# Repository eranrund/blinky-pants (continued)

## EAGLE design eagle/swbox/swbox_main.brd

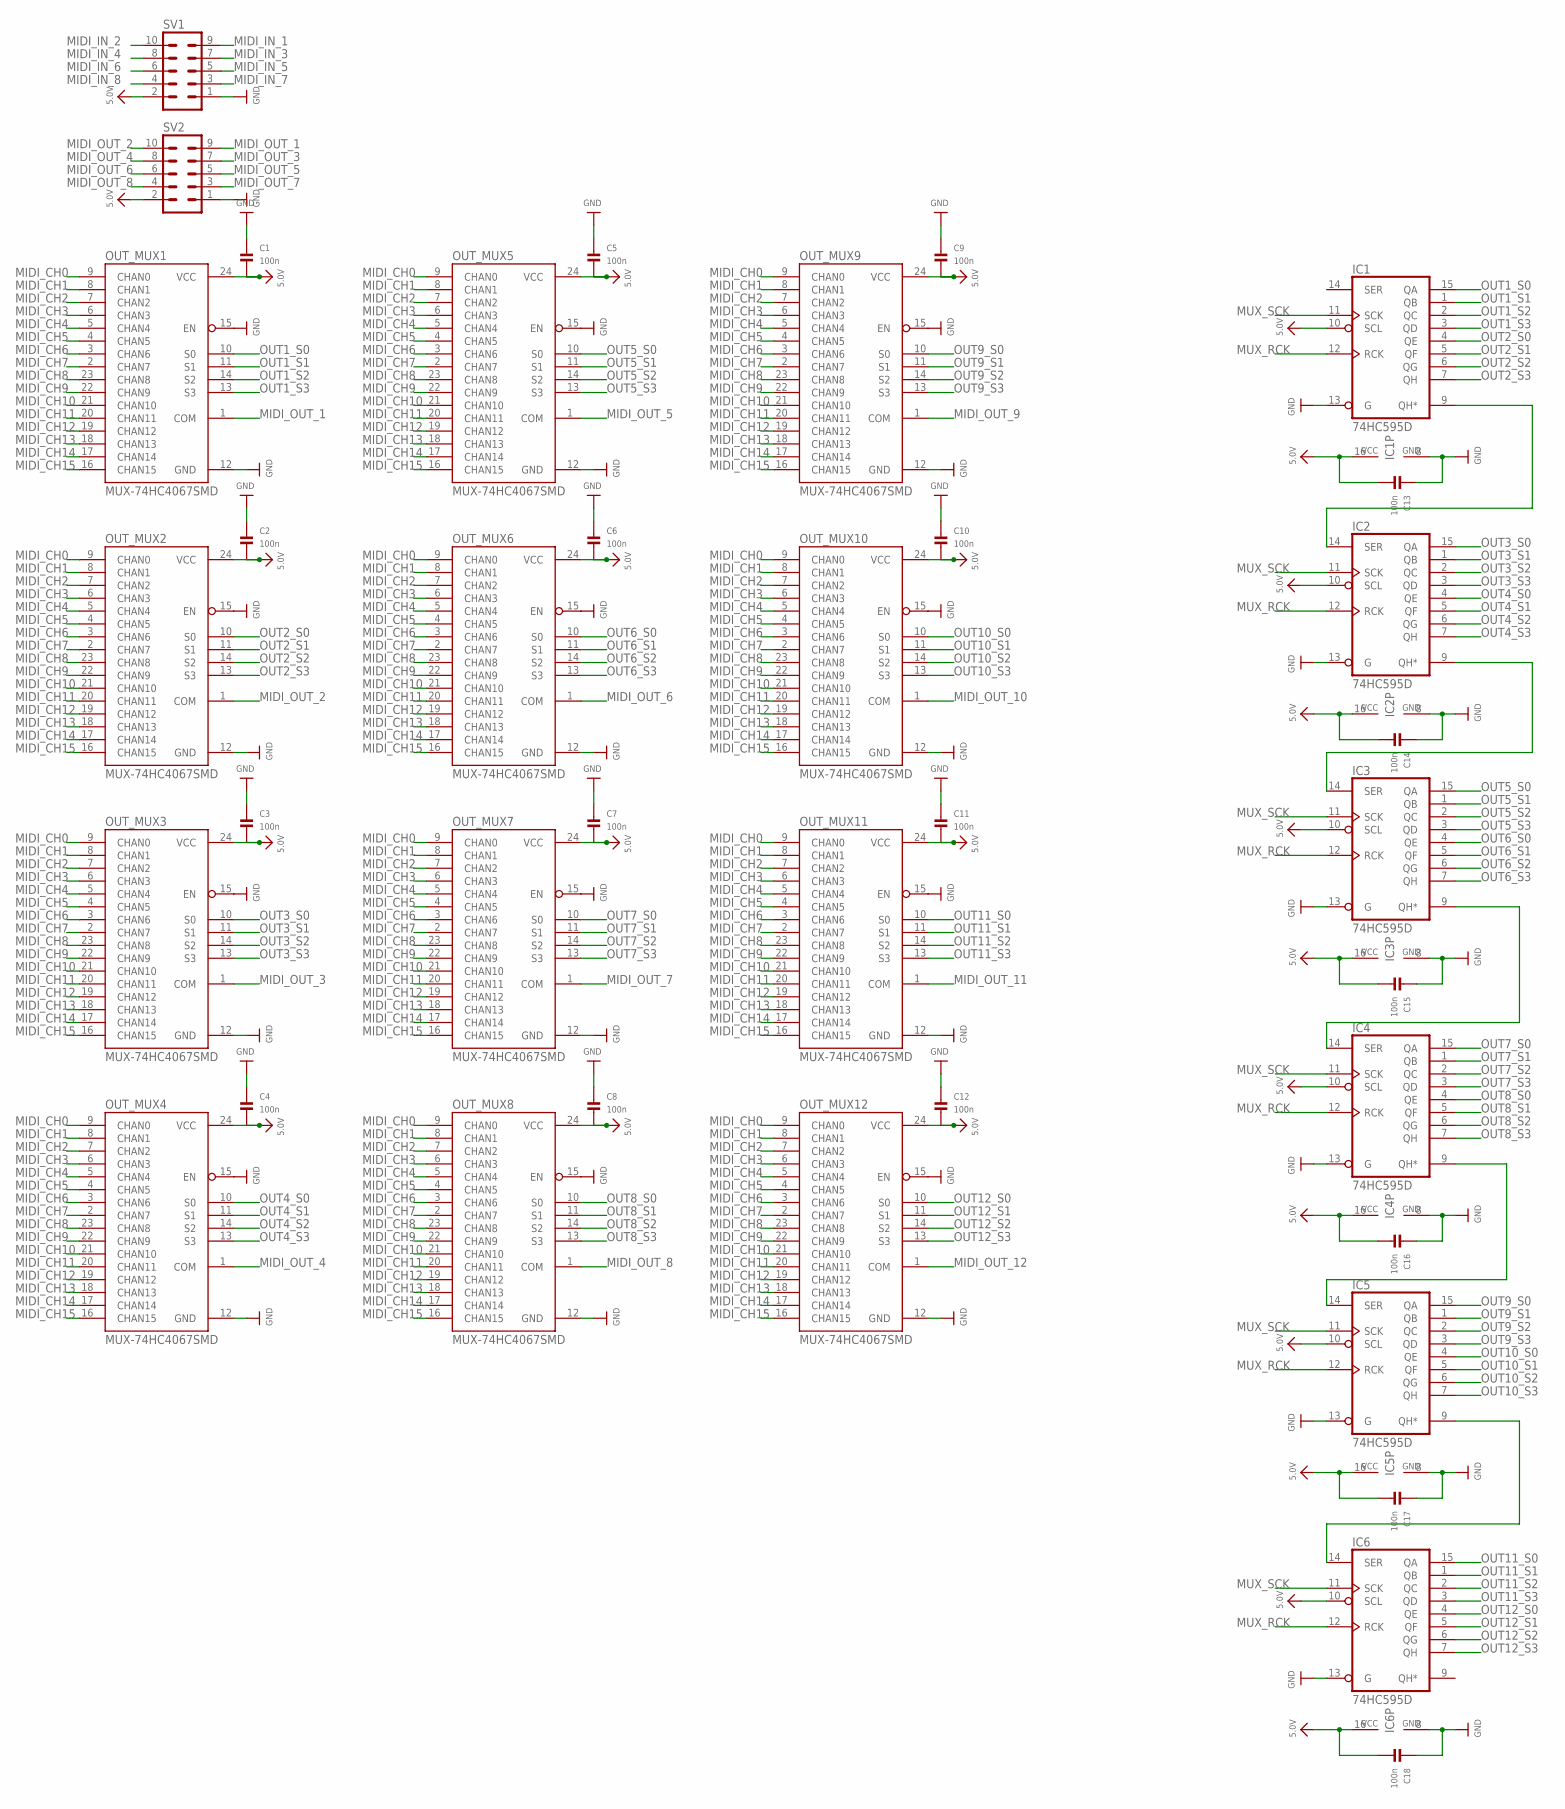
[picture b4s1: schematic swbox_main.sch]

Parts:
C1, C2, C3, C4, C5, C6, C7, C8, C9, C10, C11, C12, C13, C14, C15, C16, C17, C18: 100n; 0603
IC1, IC2, IC3, IC4, IC5, IC6: 74HC595D; SO16
OUT_MUX1, OUT_MUX2, OUT_MUX3, OUT_MUX4, OUT_MUX5, OUT_MUX6, OUT_MUX7, OUT_MUX8, OUT_MUX9, OUT_MUX10, OUT_MUX11, OUT_MUX12: MUX-74HC4067SMD; SSOP24
SV1, SV2: ML10

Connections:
5.0V: C1.2, C2.2, C3.2, C4.2, C5.2, C6.2, C7.2, C8.2, C9.2, C10.2, C11.2, C12.2, C13.2, C14.2, C15.2, C16.2, C17.2, C18.2, IC1.10 (SCL), IC1.16 (VCC), IC2.10 (SCL), IC2.16 (VCC), IC3.10 (SCL), IC3.16 (VCC), IC4.10 (SCL), IC4.16 (VCC), IC5.10 (SCL), IC5.16 (VCC), IC6.10 (SCL), IC6.16 (VCC), OUT_MUX1.24 (VCC), OUT_MUX2.24 (VCC), OUT_MUX3.24 (VCC), OUT_MUX4.24 (VCC), OUT_MUX5.24 (VCC), OUT_MUX6.24 (VCC), OUT_MUX7.24 (VCC), OUT_MUX8.24 (VCC), OUT_MUX9.24 (VCC), OUT_MUX10.24 (VCC), OUT_MUX11.24 (VCC), OUT_MUX12.24 (VCC), SV1.2, SV2.2
GND: C1.1, C2.1, C3.1, C4.1, C5.1, C6.1, C7.1, C8.1, C9.1, C10.1, C11.1, C12.1, C13.1, C14.1, C15.1, C16.1, C17.1, C18.1, IC1.8 (GND), IC1.13 (G), IC2.8 (GND), IC2.13 (G), IC3.8 (GND), IC3.13 (G), IC4.8 (GND), IC4.13 (G), IC5.8 (GND), IC5.13 (G), IC6.8 (GND), IC6.13 (G), OUT_MUX1.12 (GND), OUT_MUX1.15 (EN), OUT_MUX2.12 (GND), OUT_MUX2.15 (EN), OUT_MUX3.12 (GND), OUT_MUX3.15 (EN), OUT_MUX4.12 (GND), OUT_MUX4.15 (EN), OUT_MUX5.12 (GND), OUT_MUX5.15 (EN), OUT_MUX6.12 (GND), OUT_MUX6.15 (EN), OUT_MUX7.12 (GND), OUT_MUX7.15 (EN), OUT_MUX8.12 (GND), OUT_MUX8.15 (EN), OUT_MUX9.12 (GND), OUT_MUX9.15 (EN), OUT_MUX10.12 (GND), OUT_MUX10.15 (EN), OUT_MUX11.12 (GND), OUT_MUX11.15 (EN), OUT_MUX12.12 (GND), OUT_MUX12.15 (EN), SV1.1, SV2.1
MIDI_CH0: OUT_MUX1.9 (CHAN0), OUT_MUX2.9 (CHAN0), OUT_MUX3.9 (CHAN0), OUT_MUX4.9 (CHAN0), OUT_MUX5.9 (CHAN0), OUT_MUX6.9 (CHAN0), OUT_MUX7.9 (CHAN0), OUT_MUX8.9 (CHAN0), OUT_MUX9.9 (CHAN0), OUT_MUX10.9 (CHAN0), OUT_MUX11.9 (CHAN0), OUT_MUX12.9 (CHAN0)
MIDI_CH1: OUT_MUX1.8 (CHAN1), OUT_MUX2.8 (CHAN1), OUT_MUX3.8 (CHAN1), OUT_MUX4.8 (CHAN1), OUT_MUX5.8 (CHAN1), OUT_MUX6.8 (CHAN1), OUT_MUX7.8 (CHAN1), OUT_MUX8.8 (CHAN1), OUT_MUX9.8 (CHAN1), OUT_MUX10.8 (CHAN1), OUT_MUX11.8 (CHAN1), OUT_MUX12.8 (CHAN1)
MIDI_CH2: OUT_MUX1.7 (CHAN2), OUT_MUX2.7 (CHAN2), OUT_MUX3.7 (CHAN2), OUT_MUX4.7 (CHAN2), OUT_MUX5.7 (CHAN2), OUT_MUX6.7 (CHAN2), OUT_MUX7.7 (CHAN2), OUT_MUX8.7 (CHAN2), OUT_MUX9.7 (CHAN2), OUT_MUX10.7 (CHAN2), OUT_MUX11.7 (CHAN2), OUT_MUX12.7 (CHAN2)
MIDI_CH3: OUT_MUX1.6 (CHAN3), OUT_MUX2.6 (CHAN3), OUT_MUX3.6 (CHAN3), OUT_MUX4.6 (CHAN3), OUT_MUX5.6 (CHAN3), OUT_MUX6.6 (CHAN3), OUT_MUX7.6 (CHAN3), OUT_MUX8.6 (CHAN3), OUT_MUX9.6 (CHAN3), OUT_MUX10.6 (CHAN3), OUT_MUX11.6 (CHAN3), OUT_MUX12.6 (CHAN3)
MIDI_CH4: OUT_MUX1.5 (CHAN4), OUT_MUX2.5 (CHAN4), OUT_MUX3.5 (CHAN4), OUT_MUX4.5 (CHAN4), OUT_MUX5.5 (CHAN4), OUT_MUX6.5 (CHAN4), OUT_MUX7.5 (CHAN4), OUT_MUX8.5 (CHAN4), OUT_MUX9.5 (CHAN4), OUT_MUX10.5 (CHAN4), OUT_MUX11.5 (CHAN4), OUT_MUX12.5 (CHAN4)
MIDI_CH5: OUT_MUX1.4 (CHAN5), OUT_MUX2.4 (CHAN5), OUT_MUX3.4 (CHAN5), OUT_MUX4.4 (CHAN5), OUT_MUX5.4 (CHAN5), OUT_MUX6.4 (CHAN5), OUT_MUX7.4 (CHAN5), OUT_MUX8.4 (CHAN5), OUT_MUX9.4 (CHAN5), OUT_MUX10.4 (CHAN5), OUT_MUX11.4 (CHAN5), OUT_MUX12.4 (CHAN5)
MIDI_CH6: OUT_MUX1.3 (CHAN6), OUT_MUX2.3 (CHAN6), OUT_MUX3.3 (CHAN6), OUT_MUX4.3 (CHAN6), OUT_MUX5.3 (CHAN6), OUT_MUX6.3 (CHAN6), OUT_MUX7.3 (CHAN6), OUT_MUX8.3 (CHAN6), OUT_MUX9.3 (CHAN6), OUT_MUX10.3 (CHAN6), OUT_MUX11.3 (CHAN6), OUT_MUX12.3 (CHAN6)
MIDI_CH7: OUT_MUX1.2 (CHAN7), OUT_MUX2.2 (CHAN7), OUT_MUX3.2 (CHAN7), OUT_MUX4.2 (CHAN7), OUT_MUX5.2 (CHAN7), OUT_MUX6.2 (CHAN7), OUT_MUX7.2 (CHAN7), OUT_MUX8.2 (CHAN7), OUT_MUX9.2 (CHAN7), OUT_MUX10.2 (CHAN7), OUT_MUX11.2 (CHAN7), OUT_MUX12.2 (CHAN7)
MIDI_CH8: OUT_MUX1.23 (CHAN8), OUT_MUX2.23 (CHAN8), OUT_MUX3.23 (CHAN8), OUT_MUX4.23 (CHAN8), OUT_MUX5.23 (CHAN8), OUT_MUX6.23 (CHAN8), OUT_MUX7.23 (CHAN8), OUT_MUX8.23 (CHAN8), OUT_MUX9.23 (CHAN8), OUT_MUX10.23 (CHAN8), OUT_MUX11.23 (CHAN8), OUT_MUX12.23 (CHAN8)
MIDI_CH9: OUT_MUX1.22 (CHAN9), OUT_MUX2.22 (CHAN9), OUT_MUX3.22 (CHAN9), OUT_MUX4.22 (CHAN9), OUT_MUX5.22 (CHAN9), OUT_MUX6.22 (CHAN9), OUT_MUX7.22 (CHAN9), OUT_MUX8.22 (CHAN9), OUT_MUX9.22 (CHAN9), OUT_MUX10.22 (CHAN9), OUT_MUX11.22 (CHAN9), OUT_MUX12.22 (CHAN9)
MIDI_CH10: OUT_MUX1.21 (CHAN10), OUT_MUX2.21 (CHAN10), OUT_MUX3.21 (CHAN10), OUT_MUX4.21 (CHAN10), OUT_MUX5.21 (CHAN10), OUT_MUX6.21 (CHAN10), OUT_MUX7.21 (CHAN10), OUT_MUX8.21 (CHAN10), OUT_MUX9.21 (CHAN10), OUT_MUX10.21 (CHAN10), OUT_MUX11.21 (CHAN10), OUT_MUX12.21 (CHAN10)
MIDI_CH11: OUT_MUX1.20 (CHAN11), OUT_MUX2.20 (CHAN11), OUT_MUX3.20 (CHAN11), OUT_MUX4.20 (CHAN11), OUT_MUX5.20 (CHAN11), OUT_MUX6.20 (CHAN11), OUT_MUX7.20 (CHAN11), OUT_MUX8.20 (CHAN11), OUT_MUX9.20 (CHAN11), OUT_MUX10.20 (CHAN11), OUT_MUX11.20 (CHAN11), OUT_MUX12.20 (CHAN11)
MIDI_CH12: OUT_MUX1.19 (CHAN12), OUT_MUX2.19 (CHAN12), OUT_MUX3.19 (CHAN12), OUT_MUX4.19 (CHAN12), OUT_MUX5.19 (CHAN12), OUT_MUX6.19 (CHAN12), OUT_MUX7.19 (CHAN12), OUT_MUX8.19 (CHAN12), OUT_MUX9.19 (CHAN12), OUT_MUX10.19 (CHAN12), OUT_MUX11.19 (CHAN12), OUT_MUX12.19 (CHAN12)
MIDI_CH13: OUT_MUX1.18 (CHAN13), OUT_MUX2.18 (CHAN13), OUT_MUX3.18 (CHAN13), OUT_MUX4.18 (CHAN13), OUT_MUX5.18 (CHAN13), OUT_MUX6.18 (CHAN13), OUT_MUX7.18 (CHAN13), OUT_MUX8.18 (CHAN13), OUT_MUX9.18 (CHAN13), OUT_MUX10.18 (CHAN13), OUT_MUX11.18 (CHAN13), OUT_MUX12.18 (CHAN13)
MIDI_CH14: OUT_MUX1.17 (CHAN14), OUT_MUX2.17 (CHAN14), OUT_MUX3.17 (CHAN14), OUT_MUX4.17 (CHAN14), OUT_MUX5.17 (CHAN14), OUT_MUX6.17 (CHAN14), OUT_MUX7.17 (CHAN14), OUT_MUX8.17 (CHAN14), OUT_MUX9.17 (CHAN14), OUT_MUX10.17 (CHAN14), OUT_MUX11.17 (CHAN14), OUT_MUX12.17 (CHAN14)
MIDI_CH15: OUT_MUX1.16 (CHAN15), OUT_MUX2.16 (CHAN15), OUT_MUX3.16 (CHAN15), OUT_MUX4.16 (CHAN15), OUT_MUX5.16 (CHAN15), OUT_MUX6.16 (CHAN15), OUT_MUX7.16 (CHAN15), OUT_MUX8.16 (CHAN15), OUT_MUX9.16 (CHAN15), OUT_MUX10.16 (CHAN15), OUT_MUX11.16 (CHAN15), OUT_MUX12.16 (CHAN15)
MIDI_IN_1: SV1.9
MIDI_IN_2: SV1.10
MIDI_IN_3: SV1.7
MIDI_IN_4: SV1.8
MIDI_IN_5: SV1.5
MIDI_IN_6: SV1.6
MIDI_IN_7: SV1.3
MIDI_IN_8: SV1.4
MIDI_OUT_1: OUT_MUX1.1 (COM), SV2.9
MIDI_OUT_2: OUT_MUX2.1 (COM), SV2.10
MIDI_OUT_3: OUT_MUX3.1 (COM), SV2.7
MIDI_OUT_4: OUT_MUX4.1 (COM), SV2.8
MIDI_OUT_5: OUT_MUX5.1 (COM), SV2.5
MIDI_OUT_6: OUT_MUX6.1 (COM), SV2.6
MIDI_OUT_7: OUT_MUX7.1 (COM), SV2.3
MIDI_OUT_8: OUT_MUX8.1 (COM), SV2.4
MIDI_OUT_9: OUT_MUX9.1 (COM)
MIDI_OUT_10: OUT_MUX10.1 (COM)
MIDI_OUT_11: OUT_MUX11.1 (COM)
MIDI_OUT_12: OUT_MUX12.1 (COM)
MUX_RCK: IC1.12 (RCK), IC2.12 (RCK), IC3.12 (RCK), IC4.12 (RCK), IC5.12 (RCK), IC6.12 (RCK)
MUX_SCK: IC1.11 (SCK), IC2.11 (SCK), IC3.11 (SCK), IC4.11 (SCK), IC5.11 (SCK), IC6.11 (SCK)
unnamed: IC1.9 (QH*), IC2.14 (SER)
unnamed: IC2.9 (QH*), IC3.14 (SER)
unnamed: IC3.9 (QH*), IC4.14 (SER)
unnamed: IC4.9 (QH*), IC5.14 (SER)
unnamed: IC5.9 (QH*), IC6.14 (SER)
OUT1_S0: IC1.15 (QA), OUT_MUX1.10 (S0)
OUT1_S1: IC1.1 (QB), OUT_MUX1.11 (S1)
OUT1_S2: IC1.2 (QC), OUT_MUX1.14 (S2)
OUT1_S3: IC1.3 (QD), OUT_MUX1.13 (S3)
OUT2_S0: IC1.4 (QE), OUT_MUX2.10 (S0)
OUT2_S1: IC1.5 (QF), OUT_MUX2.11 (S1)
OUT2_S2: IC1.6 (QG), OUT_MUX2.14 (S2)
OUT2_S3: IC1.7 (QH), OUT_MUX2.13 (S3)
OUT3_S0: IC2.15 (QA), OUT_MUX3.10 (S0)
OUT3_S1: IC2.1 (QB), OUT_MUX3.11 (S1)
OUT3_S2: IC2.2 (QC), OUT_MUX3.14 (S2)
OUT3_S3: IC2.3 (QD), OUT_MUX3.13 (S3)
OUT4_S0: IC2.4 (QE), OUT_MUX4.10 (S0)
OUT4_S1: IC2.5 (QF), OUT_MUX4.11 (S1)
OUT4_S2: IC2.6 (QG), OUT_MUX4.14 (S2)
OUT4_S3: IC2.7 (QH), OUT_MUX4.13 (S3)
OUT5_S0: IC3.15 (QA), OUT_MUX5.10 (S0)
OUT5_S1: IC3.1 (QB), OUT_MUX5.11 (S1)
OUT5_S2: IC3.2 (QC), OUT_MUX5.14 (S2)
OUT5_S3: IC3.3 (QD), OUT_MUX5.13 (S3)
OUT6_S0: IC3.4 (QE), OUT_MUX6.10 (S0)
OUT6_S1: IC3.5 (QF), OUT_MUX6.11 (S1)
OUT6_S2: IC3.6 (QG), OUT_MUX6.14 (S2)
OUT6_S3: IC3.7 (QH), OUT_MUX6.13 (S3)
OUT7_S0: IC4.15 (QA), OUT_MUX7.10 (S0)
OUT7_S1: IC4.1 (QB), OUT_MUX7.11 (S1)
OUT7_S2: IC4.2 (QC), OUT_MUX7.14 (S2)
OUT7_S3: IC4.3 (QD), OUT_MUX7.13 (S3)
OUT8_S0: IC4.4 (QE), OUT_MUX8.10 (S0)
OUT8_S1: IC4.5 (QF), OUT_MUX8.11 (S1)
OUT8_S2: IC4.6 (QG), OUT_MUX8.14 (S2)
OUT8_S3: IC4.7 (QH), OUT_MUX8.13 (S3)
OUT9_S0: IC5.15 (QA), OUT_MUX9.10 (S0)
OUT9_S1: IC5.1 (QB), OUT_MUX9.11 (S1)
OUT9_S2: IC5.2 (QC), OUT_MUX9.14 (S2)
OUT9_S3: IC5.3 (QD), OUT_MUX9.13 (S3)
OUT10_S0: IC5.4 (QE), OUT_MUX10.10 (S0)
OUT10_S1: IC5.5 (QF), OUT_MUX10.11 (S1)
OUT10_S2: IC5.6 (QG), OUT_MUX10.14 (S2)
OUT10_S3: IC5.7 (QH), OUT_MUX10.13 (S3)
OUT11_S0: IC6.15 (QA), OUT_MUX11.10 (S0)
OUT11_S1: IC6.1 (QB), OUT_MUX11.11 (S1)
OUT11_S2: IC6.2 (QC), OUT_MUX11.14 (S2)
OUT11_S3: IC6.3 (QD), OUT_MUX11.13 (S3)
OUT12_S0: IC6.4 (QE), OUT_MUX12.10 (S0)
OUT12_S1: IC6.5 (QF), OUT_MUX12.11 (S1)
OUT12_S2: IC6.6 (QG), OUT_MUX12.14 (S2)
OUT12_S3: IC6.7 (QH), OUT_MUX12.13 (S3)

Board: 2 copper layers, 38 parts (0 on the bottom side), 81 nets, no tracks yet.

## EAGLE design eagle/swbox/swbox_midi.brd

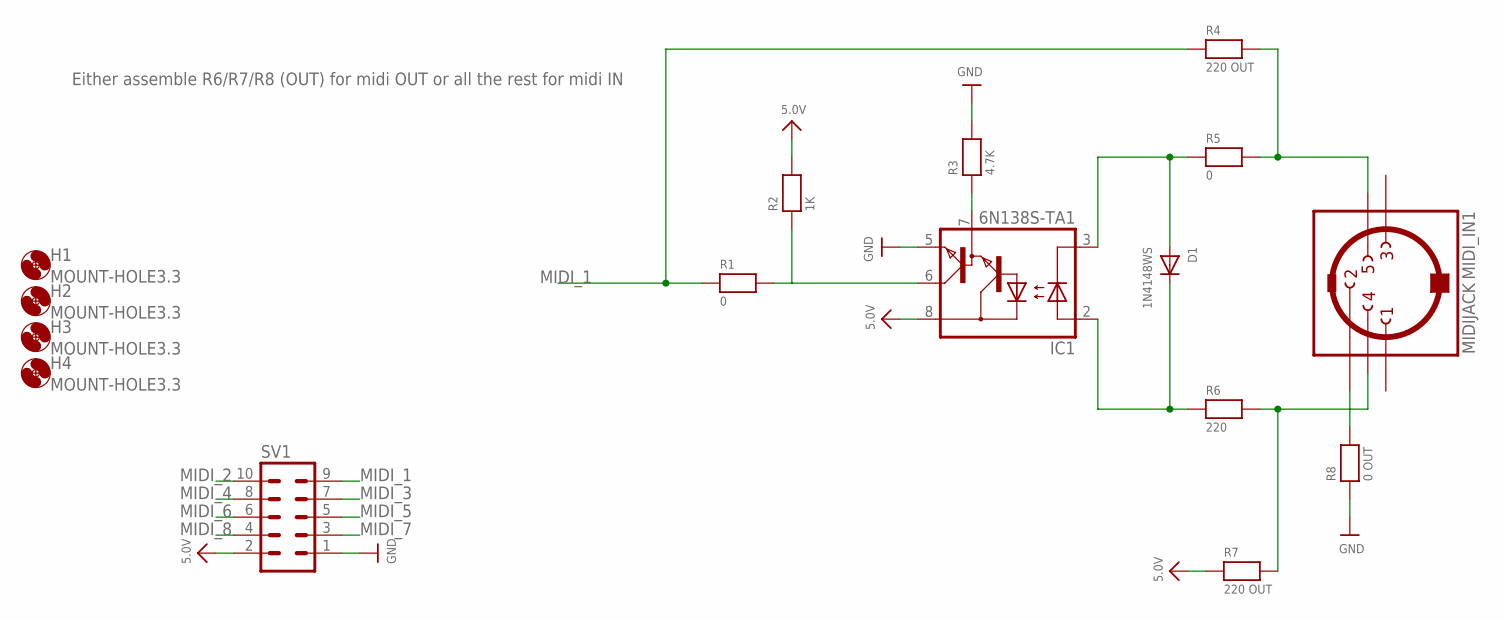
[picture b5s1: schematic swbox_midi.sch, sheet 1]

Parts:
D1: 1N4148WS; SOD-323
H1, H2, H3, H4: MOUNT-HOLE3.3; 3,3
IC1: 6N138S-TA1; SO8-GW300
MIDI_IN1: MIDIJACK; CP-2350
R1, R5: 0; _0603
R2: 1K; _0603
R3: 4.7K; _0603
R4, R7: 220 OUT; _0603
R6: 220; _0603
R8: 0 OUT; _0603
SV1: ML10

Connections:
5.0V: IC1.8 (VCC), R2.2, R7.1, SV1.2; also elsewhere on the board
GND: IC1.5 (GND), R3.2, R8.1, SV1.1; also elsewhere on the board
MIDI_1: R1.1, R4.1, SV1.9
MIDI_2: SV1.10; also elsewhere on the board
MIDI_3: SV1.7; also elsewhere on the board
MIDI_4: SV1.8; also elsewhere on the board
MIDI_5: SV1.5; also elsewhere on the board
MIDI_6: SV1.6; also elsewhere on the board
MIDI_7: SV1.3; also elsewhere on the board
MIDI_8: SV1.4; also elsewhere on the board
unnamed: IC1.6 (VO), R1.2, R2.1
unnamed: MIDI_IN1.4, R6.2, R7.2
unnamed: D1.C, IC1.2 (A), R6.1
unnamed: D1.A, IC1.3 (C), R5.1
unnamed: IC1.7 (VB), R3.1
unnamed: MIDI_IN1.5, R4.2, R5.2
unnamed: MIDI_IN1.2, R8.2

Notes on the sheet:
Either assemble R6/R7/R8 (OUT) for midi OUT or all the rest for midi IN

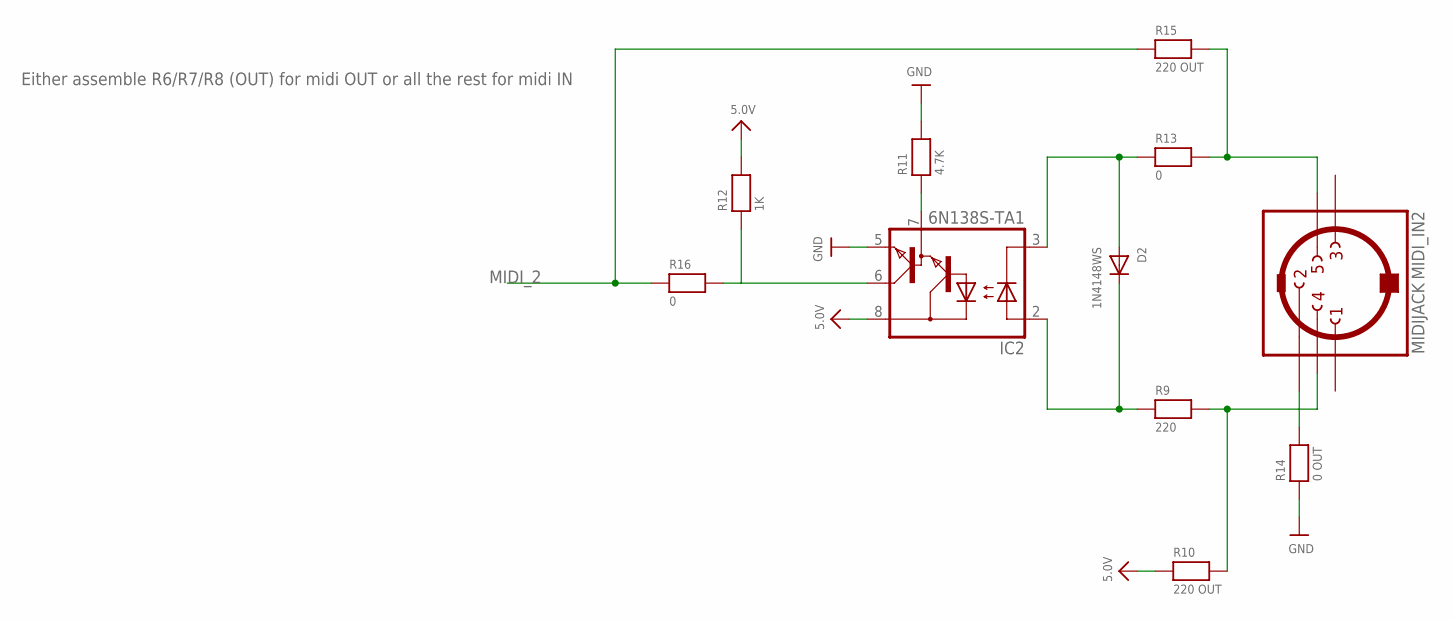
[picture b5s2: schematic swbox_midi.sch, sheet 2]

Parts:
D2: 1N4148WS; SOD-323
IC2: 6N138S-TA1; SO8-GW300
MIDI_IN2: MIDIJACK; CP-2350
R9: 220; _0603
R10, R15: 220 OUT; _0603
R11: 4.7K; _0603
R12: 1K; _0603
R13, R16: 0; _0603
R14: 0 OUT; _0603

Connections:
5.0V: IC2.8 (VCC), R10.1, R12.2; also elsewhere on the board
GND: IC2.5 (GND), R11.2, R14.1; also elsewhere on the board
MIDI_2: R15.1, R16.1; also elsewhere on the board
unnamed: MIDI_IN2.4, R9.2, R10.2
unnamed: D2.C, IC2.2 (A), R9.1
unnamed: D2.A, IC2.3 (C), R13.1
unnamed: IC2.7 (VB), R11.1
unnamed: IC2.6 (VO), R12.1, R16.2
unnamed: MIDI_IN2.5, R13.2, R15.2
unnamed: MIDI_IN2.2, R14.2

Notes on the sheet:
Either assemble R6/R7/R8 (OUT) for midi OUT or all the rest for midi IN

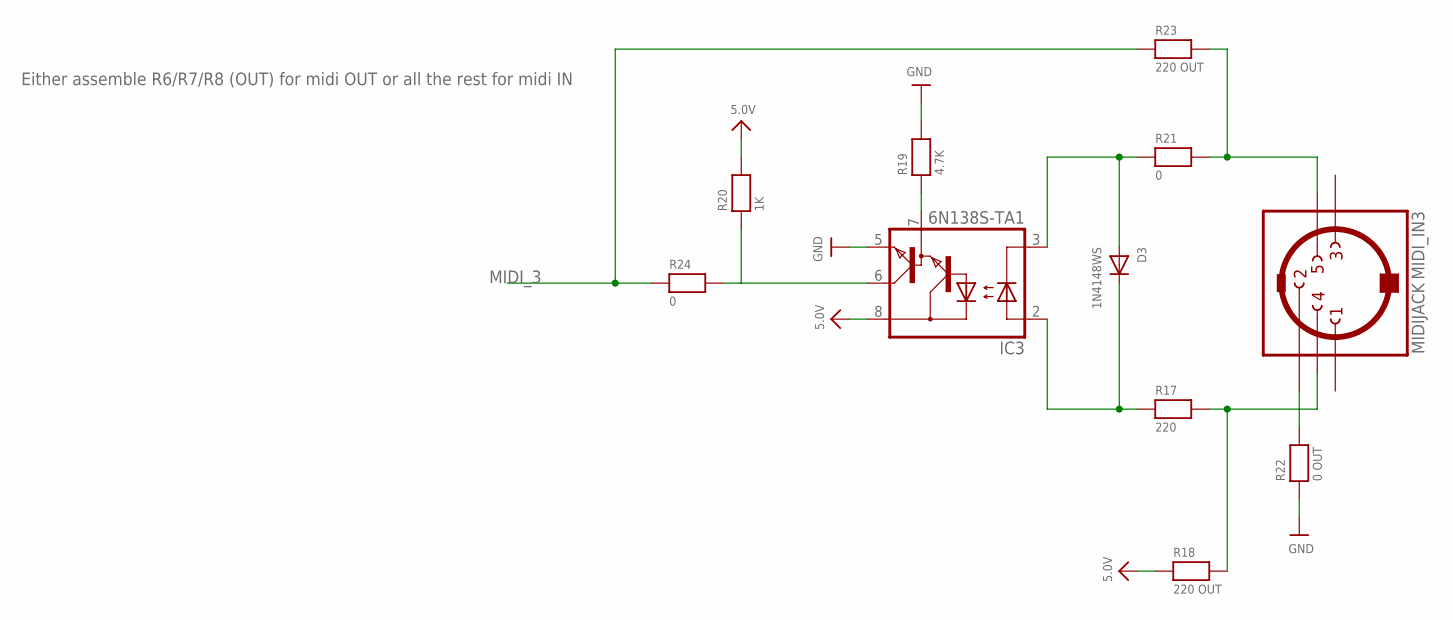
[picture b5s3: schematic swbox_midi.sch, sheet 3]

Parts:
D3: 1N4148WS; SOD-323
IC3: 6N138S-TA1; SO8-GW300
MIDI_IN3: MIDIJACK; CP-2350
R17: 220; _0603
R18, R23: 220 OUT; _0603
R19: 4.7K; _0603
R20: 1K; _0603
R21, R24: 0; _0603
R22: 0 OUT; _0603

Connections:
5.0V: IC3.8 (VCC), R18.1, R20.2; also elsewhere on the board
GND: IC3.5 (GND), R19.2, R22.1; also elsewhere on the board
MIDI_3: R23.1, R24.1; also elsewhere on the board
unnamed: MIDI_IN3.4, R17.2, R18.2
unnamed: D3.C, IC3.2 (A), R17.1
unnamed: D3.A, IC3.3 (C), R21.1
unnamed: IC3.7 (VB), R19.1
unnamed: IC3.6 (VO), R20.1, R24.2
unnamed: MIDI_IN3.5, R21.2, R23.2
unnamed: MIDI_IN3.2, R22.2

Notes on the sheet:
Either assemble R6/R7/R8 (OUT) for midi OUT or all the rest for midi IN

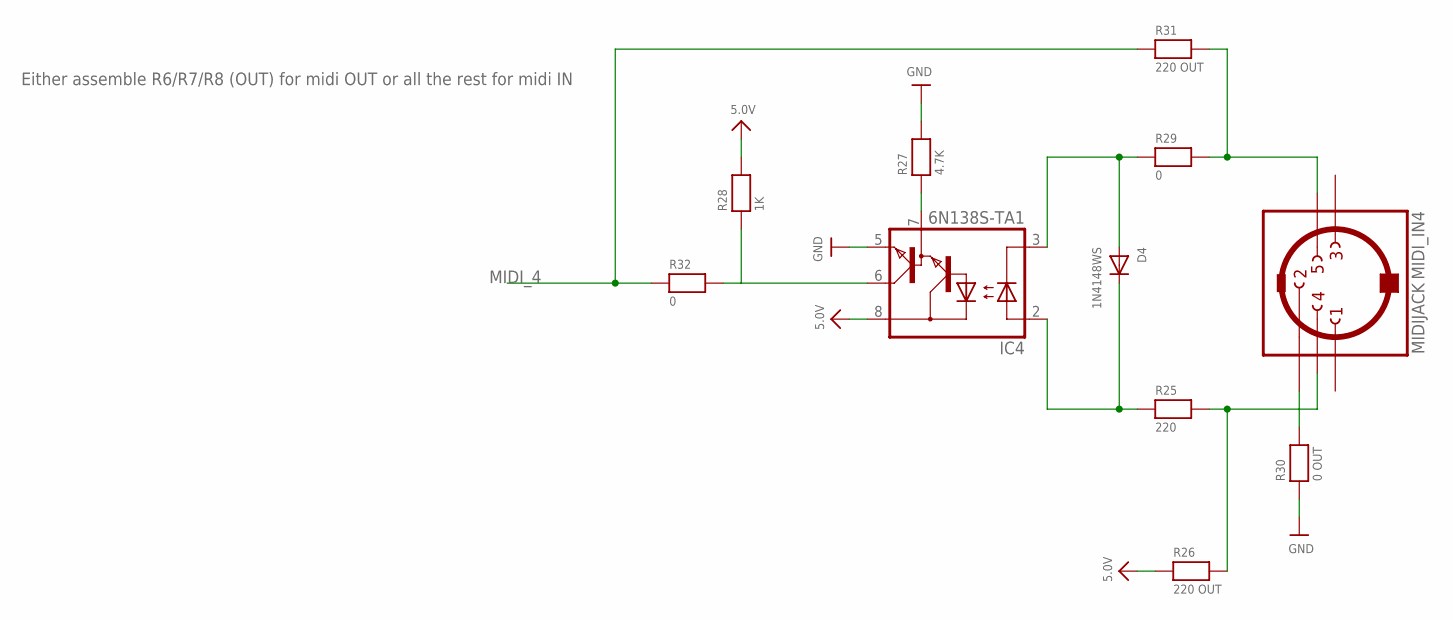
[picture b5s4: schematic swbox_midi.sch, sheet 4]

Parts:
D4: 1N4148WS; SOD-323
IC4: 6N138S-TA1; SO8-GW300
MIDI_IN4: MIDIJACK; CP-2350
R25: 220; _0603
R26, R31: 220 OUT; _0603
R27: 4.7K; _0603
R28: 1K; _0603
R29, R32: 0; _0603
R30: 0 OUT; _0603

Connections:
5.0V: IC4.8 (VCC), R26.1, R28.2; also elsewhere on the board
GND: IC4.5 (GND), R27.2, R30.1; also elsewhere on the board
MIDI_4: R31.1, R32.1; also elsewhere on the board
unnamed: MIDI_IN4.4, R25.2, R26.2
unnamed: D4.C, IC4.2 (A), R25.1
unnamed: D4.A, IC4.3 (C), R29.1
unnamed: IC4.7 (VB), R27.1
unnamed: IC4.6 (VO), R28.1, R32.2
unnamed: MIDI_IN4.5, R29.2, R31.2
unnamed: MIDI_IN4.2, R30.2

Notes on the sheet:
Either assemble R6/R7/R8 (OUT) for midi OUT or all the rest for midi IN

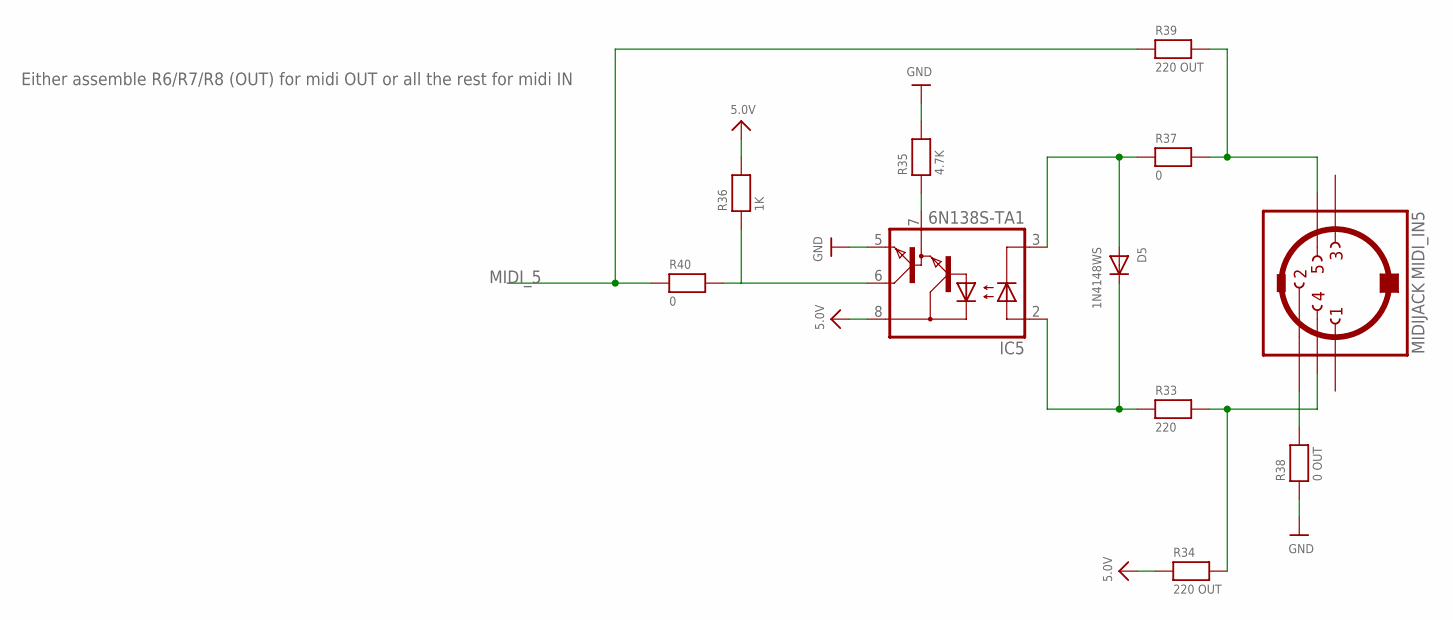
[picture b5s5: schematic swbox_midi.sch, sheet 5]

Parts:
D5: 1N4148WS; SOD-323
IC5: 6N138S-TA1; SO8-GW300
MIDI_IN5: MIDIJACK; CP-2350
R33: 220; _0603
R34, R39: 220 OUT; _0603
R35: 4.7K; _0603
R36: 1K; _0603
R37, R40: 0; _0603
R38: 0 OUT; _0603

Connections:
5.0V: IC5.8 (VCC), R34.1, R36.2; also elsewhere on the board
GND: IC5.5 (GND), R35.2, R38.1; also elsewhere on the board
MIDI_5: R39.1, R40.1; also elsewhere on the board
unnamed: MIDI_IN5.4, R33.2, R34.2
unnamed: D5.C, IC5.2 (A), R33.1
unnamed: D5.A, IC5.3 (C), R37.1
unnamed: IC5.7 (VB), R35.1
unnamed: IC5.6 (VO), R36.1, R40.2
unnamed: MIDI_IN5.5, R37.2, R39.2
unnamed: MIDI_IN5.2, R38.2

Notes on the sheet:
Either assemble R6/R7/R8 (OUT) for midi OUT or all the rest for midi IN

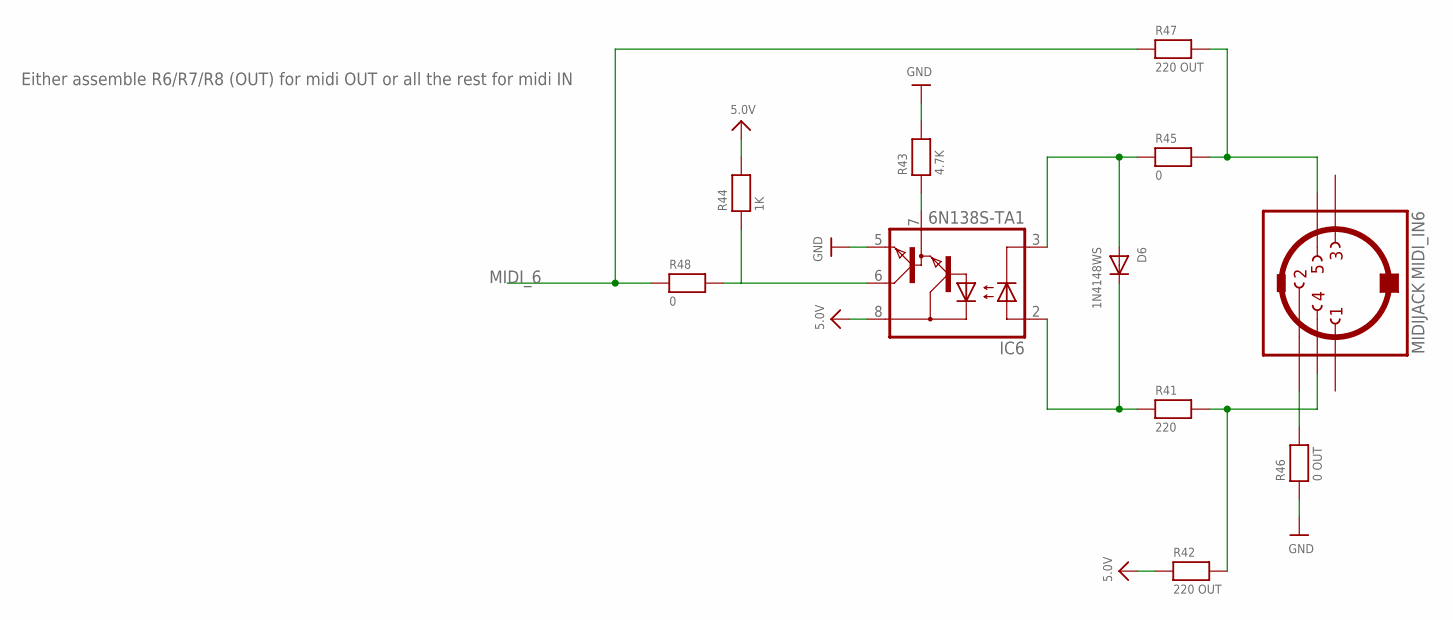
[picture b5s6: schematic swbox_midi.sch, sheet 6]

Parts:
D6: 1N4148WS; SOD-323
IC6: 6N138S-TA1; SO8-GW300
MIDI_IN6: MIDIJACK; CP-2350
R41: 220; _0603
R42, R47: 220 OUT; _0603
R43: 4.7K; _0603
R44: 1K; _0603
R45, R48: 0; _0603
R46: 0 OUT; _0603

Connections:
5.0V: IC6.8 (VCC), R42.1, R44.2; also elsewhere on the board
GND: IC6.5 (GND), R43.2, R46.1; also elsewhere on the board
MIDI_6: R47.1, R48.1; also elsewhere on the board
unnamed: MIDI_IN6.4, R41.2, R42.2
unnamed: D6.C, IC6.2 (A), R41.1
unnamed: D6.A, IC6.3 (C), R45.1
unnamed: IC6.7 (VB), R43.1
unnamed: IC6.6 (VO), R44.1, R48.2
unnamed: MIDI_IN6.5, R45.2, R47.2
unnamed: MIDI_IN6.2, R46.2

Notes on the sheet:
Either assemble R6/R7/R8 (OUT) for midi OUT or all the rest for midi IN

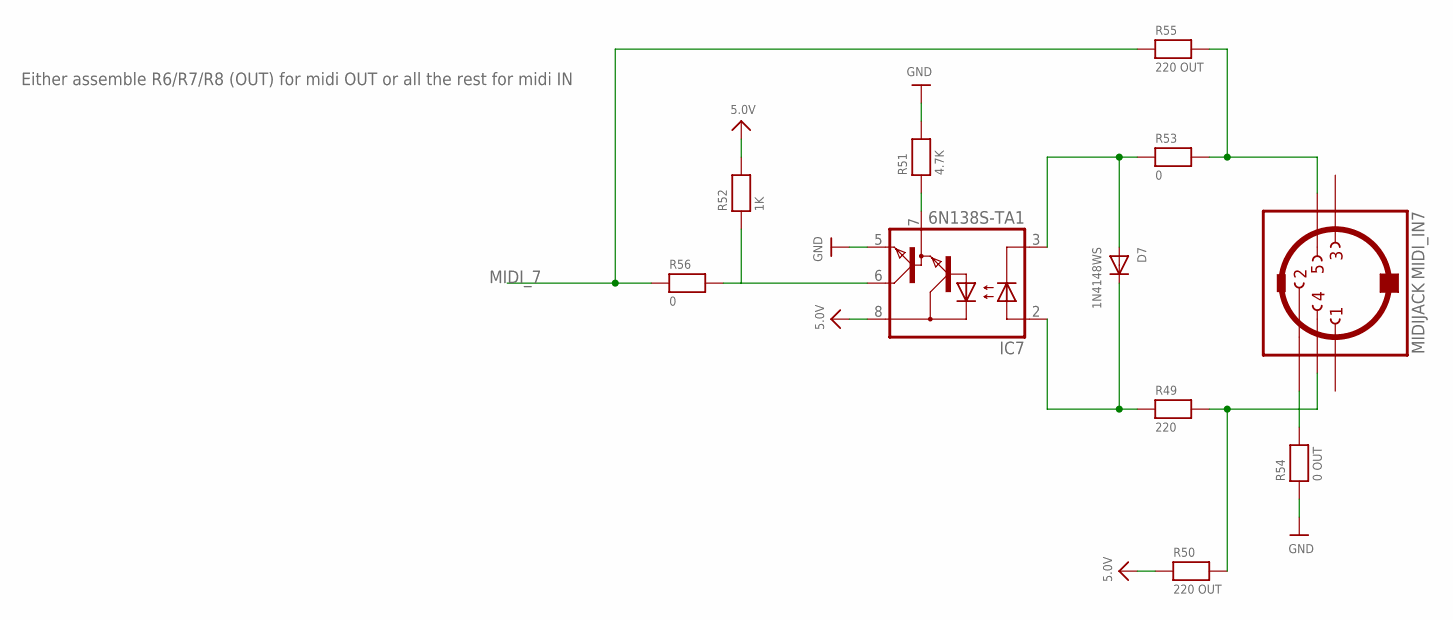
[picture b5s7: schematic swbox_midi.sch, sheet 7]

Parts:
D7: 1N4148WS; SOD-323
IC7: 6N138S-TA1; SO8-GW300
MIDI_IN7: MIDIJACK; CP-2350
R49: 220; _0603
R50, R55: 220 OUT; _0603
R51: 4.7K; _0603
R52: 1K; _0603
R53, R56: 0; _0603
R54: 0 OUT; _0603

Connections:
5.0V: IC7.8 (VCC), R50.1, R52.2; also elsewhere on the board
GND: IC7.5 (GND), R51.2, R54.1; also elsewhere on the board
MIDI_7: R55.1, R56.1; also elsewhere on the board
unnamed: MIDI_IN7.4, R49.2, R50.2
unnamed: D7.C, IC7.2 (A), R49.1
unnamed: D7.A, IC7.3 (C), R53.1
unnamed: IC7.7 (VB), R51.1
unnamed: IC7.6 (VO), R52.1, R56.2
unnamed: MIDI_IN7.5, R53.2, R55.2
unnamed: MIDI_IN7.2, R54.2

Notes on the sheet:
Either assemble R6/R7/R8 (OUT) for midi OUT or all the rest for midi IN

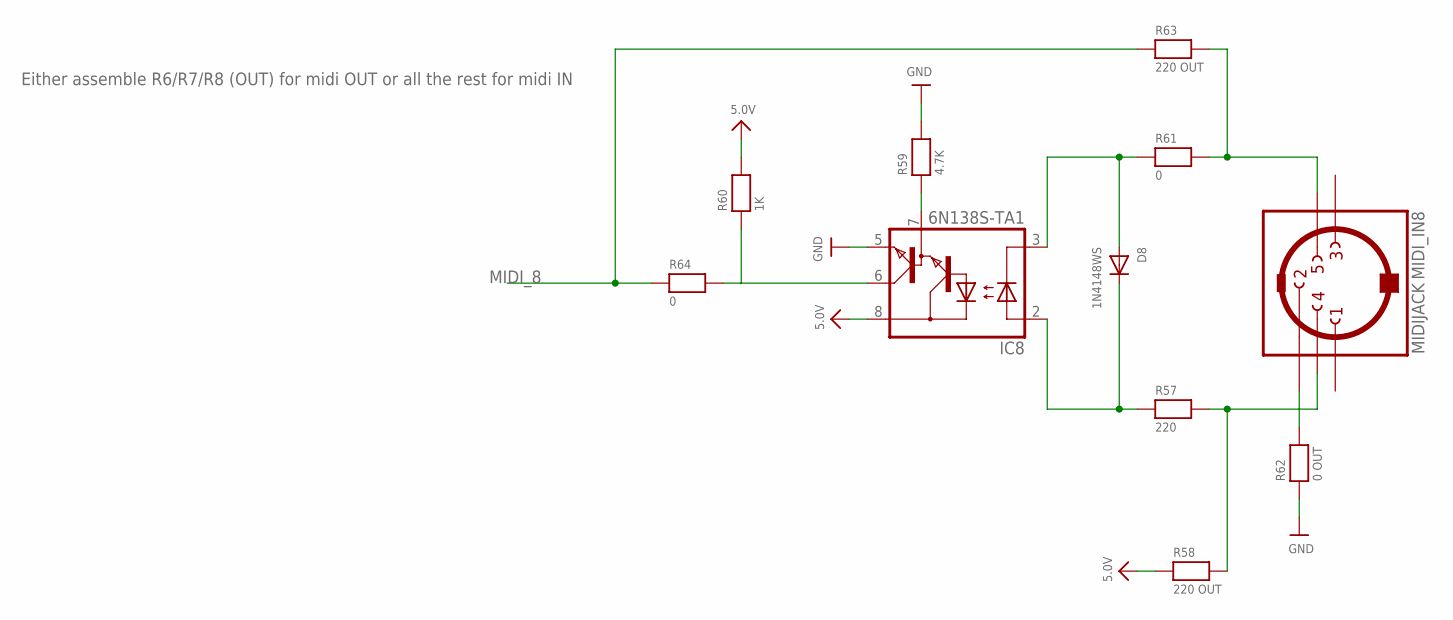
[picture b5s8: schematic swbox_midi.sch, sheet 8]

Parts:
D8: 1N4148WS; SOD-323
IC8: 6N138S-TA1; SO8-GW300
MIDI_IN8: MIDIJACK; CP-2350
R57: 220; _0603
R58, R63: 220 OUT; _0603
R59: 4.7K; _0603
R60: 1K; _0603
R61, R64: 0; _0603
R62: 0 OUT; _0603

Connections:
5.0V: IC8.8 (VCC), R58.1, R60.2; also elsewhere on the board
GND: IC8.5 (GND), R59.2, R62.1; also elsewhere on the board
MIDI_8: R63.1, R64.1; also elsewhere on the board
unnamed: MIDI_IN8.4, R57.2, R58.2
unnamed: D8.C, IC8.2 (A), R57.1
unnamed: D8.A, IC8.3 (C), R61.1
unnamed: IC8.7 (VB), R59.1
unnamed: IC8.6 (VO), R60.1, R64.2
unnamed: MIDI_IN8.5, R61.2, R63.2
unnamed: MIDI_IN8.2, R62.2

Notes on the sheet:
Either assemble R6/R7/R8 (OUT) for midi OUT or all the rest for midi IN

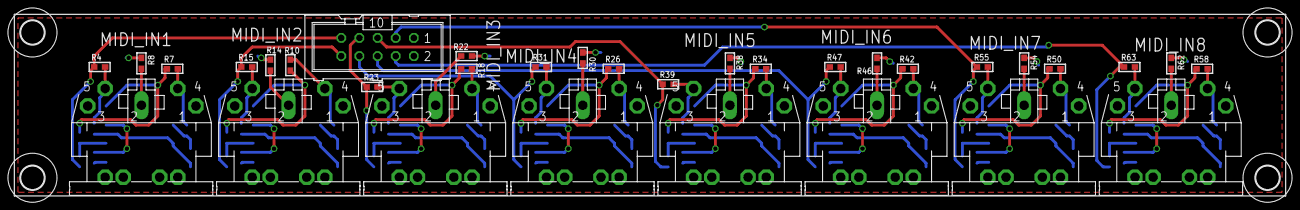
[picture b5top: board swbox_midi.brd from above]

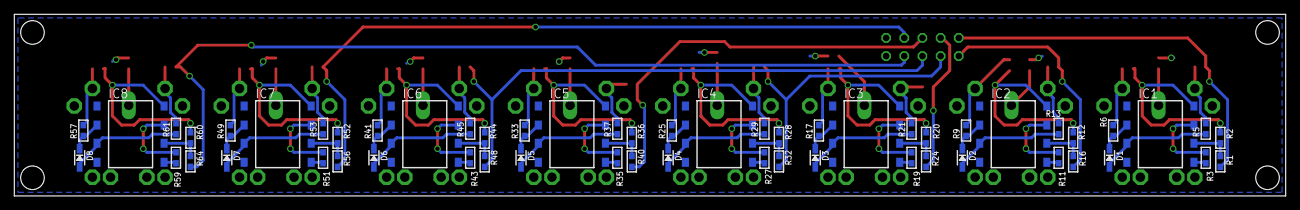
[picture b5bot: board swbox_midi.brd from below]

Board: 2 copper layers, 177.8 x 25.4 mm, 93 parts (56 on the bottom side), 66 nets.
